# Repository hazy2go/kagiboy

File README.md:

<p align="center">
  <picture>
    <source media="(prefers-color-scheme: dark)" srcset="docs/media/logo-white.png">
    
  </picture>
</p>

<p align="center">
  A hardware wallet that lives in a Game Boy cartridge.<br>
  <a href="https://kagiboy.xyz/demo"><b>Try the live demo</b></a> &nbsp;·&nbsp;
  <a href="https://kagiboy.xyz">Website</a> &nbsp;·&nbsp;
  <a href="https://kagiboy.xyz/about">The story</a> &nbsp;·&nbsp;
  <a href="docs/protocol.md">Protocol</a>
</p>

My dad found my first Game Boy at a flea market. These days the things I care most about are numbers on a phone, and the phone that asks me to approve a transaction is the same phone that tells me what I'm approving. If it lies, I sign the lie.

A Game Boy can't lie to you like that. It has no network, no apps and no operating system. It's a screen and some buttons. So kagiboy puts the keys in a cartridge and uses the Game Boy as the one screen you trust: the cartridge reads every request itself, puts the amount and the full address on that little LCD, and signs only after you hold A. The phone just builds transactions and broadcasts them. It never sees a key.

This repo has all of it: the Game Boy ROM, the cartridge's chip (simulated for now), the phone app, the website, the 3D model and the videos.

> **Status, honestly.** The software is real and runs on testnets today: Solana devnet and five EVM testnets. The ROM runs on a real Game Boy from a flash cart and in your browser. The cartridge itself is in the works; until it ships, its key chip is simulated in the browser. The parts and the plan are in [docs/hardware.md](docs/hardware.md). Please don't put a real recovery phrase anywhere near this.

## Updates

**2026-10-15: the cartridge board.** kagiboy now has its own board, in [`hardware/cart`](hardware/cart/README.md). It's built on our open [WiFi Game Boy Cartridge](https://github.com/hazy2go/wifi-game-boy-cartridge):
- an RP2350B serves the Game Boy's bus;
- an NXP SE050E2 secure element holds the keys and signs;
- a LIS3DH accelerometer adds shake entropy;
- an ESP32-C3 on its own chip does Bluetooth to the phone, so the radio stack never shares a processor with the wallet;
- a power stage that can't pull the Game Boy's 5 V below 4.588 V.

It's placed and routed, and it passes every design check and simulation: ERC/DRC, schematic-to-board parity, I²C and power calculations, the transistor-level power audits, and the cycle-level bus simulation with the real ROM. It isn't ordered yet: one inductor is out of stock at JLC.

**2026-10-15: the cartridge firmware, first part.** [`firmware/rp2350`](firmware/rp2350/README.md), Rust, MIT:
- **The wallet logic,** ported from the browser chip. It's checked against recorded sessions of the browser chip
  and gives identical bytes: every reply, refusal and signature.
- **The firmware that serves the Game Boy bus** with the exact PIO programs the cycle-level simulation validated
  for this board.

**2026-10-15: keys in the secure element.** At setup the firmware imports the two account keys into the NXP SE050
as keys that can only sign, makes the PIN an SE050 object that allows five attempts, and keeps no recovery words. A
key signs only inside a session opened with that PIN. The SE050 driver is our own, MIT. Without a chip, it's tested
against a behavioural SE050 model: every recorded browser session replays through it byte for byte.

**2026-10-15: the Bluetooth link.** The phone app can now talk to a real cartridge: "Use a real cartridge" on the
connect screen (Chrome or Edge, on a computer or Android). Messages go phone → Bluetooth LE → the ESP32-C3, which
passes them over SPI to the RP2350, unchanged. The wallet answers and the reply comes back the same way. The ESP never
sees a key or a PIN. Spec: [docs/phone-link.md](docs/phone-link.md). Every phone call of the recorded sessions goes
through the whole chain in the tests: the web app's bytes, the ESP's C code and the RP2350's Rust code, with damaged
and missed transfers and restarts on both chips. Every reply matches the browser chip's. Not yet run on hardware.

**2026-10-15: the accelerometer.** The LIS3DH is read at 100 Hz into the Game Boy's mailbox, at the same scale the
browser demo gets from the phone's motion sensor, so the ROM's "shake it" step works the same on the real cartridge.
With that, every part of the board has firmware.

**2026-10-16: JLC manufacturability check.** A new gate runs KiCad's DRC at JLCPCB's published 6-layer limits
instead of comparing against the WiFi board. It found three things the WiFi board also has, now fixed:
- a row of ground vias 0.01 mm too close to the top edge;
- ground planes that came within 0.12 mm of the edge;
- the repo URL on the back at 0.8 mm text (JLC's minimum is 1 mm).

The board passes, and the gerbers are regenerated. Every other check, simulation and test was re-run and passes.

**2026-10-16: an independent review against the datasheets.** A fresh reviewer, without our notes or checks,
went through the schematic and board pin by pin against every datasheet. It found problems our checks couldn't
see, and they're fixed:
- the Bluetooth radio's ground was connected but weak (long thin traces, 3 vias in the whole area): it now has a
  ground pour and 77 more vias;
- copper sat under the RP2350's own regulator, which its datasheet forbids on multi-layer boards: cut away, and two
  traces re-routed around it;
- one resistor JLC couldn't supply (swapped for the same value in stock), a missing pull-down on the level shifter,
  and the crystal Raspberry Pi recommends instead of a higher-resistance one;
- the 480 Mb/s USB lines now run side by side on one layer over solid ground.

Everything else it checked came out right. Details in [the logbook](hardware/cart/LOGBOOK.md).

**2026-10-16: the first order is 2 boards.** The parts check now counts stock for 2 assembled boards. Everything
is in stock except the RP2350's regulator inductor (4 left at JLC, we need 7 with spares). We're keeping that exact
part and waiting for a restock.

Next: building the board. It waits for one inductor to come back in stock at JLC. Then firmware on real hardware.

## See it work

<table>
  <tr>
    <td width="62%"></td>
    <td width="38%"></td>
  </tr>
  <tr>
    <td>The phone asks for 0.05 SOL. The Game Boy shows what the chip decoded.</td>
    <td>Hold A for a second. Signed, then confirmed on devnet.</td>
  </tr>
</table>

That transfer is a real devnet transaction: [GeVGY7kn…wEM7BDtK on the Solana explorer](https://explorer.solana.com/tx/GeVGY7kn36SS1aoRXbDQo8WiwukHD4XpPiuzs3X6jpgkfGJWR1dPgesg2B4Dwk2wuS7ngjqYkWEWH11wEM7BDtK?cluster=devnet). Same signature the Game Boy printed.

## Try it

Open **[kagiboy.xyz/demo](https://kagiboy.xyz/demo)**, on a laptop or a phone. It takes about two minutes.

1. Switch on, press Start, pick **New wallet**.
2. Mash buttons, then hold **shake**. Write down the 12 words (they're test words, but play along) and pick a PIN.
3. In the phone app, tap **Pair cartridge**. The same six digits show up on both screens. Press A.
4. Get some devnet SOL with **Get test SOL**, then **Send**. Read what the Game Boy says, hold A.

Keys on a laptop: arrows, `X` = A, `Z` = B, `Enter` = Start, `Shift` = Select. On a phone, tap the console. The bus monitor under the Game Boy shows every message between the console and the chip, with the PIN and the words blanked out.

## How it works

There are three parts, and only the cartridge ever holds a key.

The Game Boy ROM (`rom/`, C with GBDK-2020) is the screen and the buttons. It never touches a key. A Game Boy has exactly one wire to the outside world, the cartridge slot, so that's what we use: the ROM writes a command into a 256-byte mailbox in cartridge memory, and the chip writes its answer back into the same window. Each side owns its own bytes, and the sequence number is written last, so a half-written reply is never read. The commands are in [docs/protocol.md](docs/protocol.md).

The cartridge chip (`web/src/chip/`) holds the keys, counts PIN tries, keeps a network allowlist and its own token list, and decodes and signs. In the demo it's TypeScript running in your browser. On the real cartridge it's an RP2350 with the keys in an NXP SE050 secure element.

The phone app (`web/src/phone/`, `web/src/app/`) talks to the networks: balances, building transactions, broadcasting them. It reaches the chip over Bluetooth on hardware (a function call in the demo) and only ever gets public data back. It's never trusted.

### Signing on Solana

This is the part I care about most. The phone builds a normal `SystemProgram.transfer` and hands over the serialized message bytes, nothing else. The chip copies those bytes, so nothing can change them later, and decodes them itself: the fee payer has to be this cartridge, there has to be exactly one instruction, it has to be a plain transfer from this wallet, and the amount and full address have to fit on the Game Boy screen. If any of that fails, there's no prompt at all. You hold A, the chip signs those exact bytes with ed25519, and the phone broadcasts.

The phone can't fake the result either. It reports a status, but the Game Boy only shows "confirmed" next to the signature the chip itself produced (`setTxStatus` in [chip.ts](web/src/chip/chip.ts)).

### Keys

Every button press and every shake goes to the chip as entropy and gets folded into a SHA-256 pool, which is mixed with the chip's own random generator when the wallet is created. Out come 12 standard BIP-39 words. Solana keys use SLIP-10 ed25519 on Phantom's path (`m/44'/501'/0'/0'`), EVM keys use MetaMask's (`m/44'/60'/0'/0/0`), so the words restore in any normal wallet. The PIN is entered twice and stored salted and hashed. Five wrong tries and the cartridge wipes itself, like a Ledger.

### What it refuses

If the chip can't show something in full, it won't sign it. Those are the chip's real error messages, captured by sending it those requests.

### EVM and swaps

The same 12 words cover Ethereum Sepolia, Base Sepolia, Arbitrum Sepolia, HyperEVM testnet and Robinhood Chain testnet, and LEFT/RIGHT on the Game Boy switches between them. The chip checks the chain id against its allowlist and refuses any fee above 0.01 of the network's coin.

Swaps come from the [SODAX](https://sodax.com) SDK with live quotes. The phone only names tokens by address; symbols, decimals and fees come from the cartridge's own list ([tokens.ts](web/src/chip/tokens.ts)), and the Game Boy shows the least you'll get, after every fee. In the demo, swaps are signed but never sent.

## It runs on a real Game Boy

These are photos of my own DMG running the ROM from an EverDrive. A flash cart has no key chip, so `make demo` builds the prototype with a test chip inside the ROM, generated from the real chip code. It saves the wallet and PIN to the cartridge's battery RAM and plays a little chiptune of mine on the menus. It holds no real keys; it's there so the whole flow can be walked through on a real Game Boy while the cartridge is in the works.

## Build it

The ROM needs [GBDK-2020](https://github.com/gbdk-2020/gbdk-2020). The Makefile looks in `~/gbdk`; override it with `make GBDK=/path/to/gbdk`.

```sh
cd rom
make          # build/wallet.gb, also copied to web/public/wallet.gb
make demo     # build/wallet-demo.gb, the flash-cart prototype build
```

The website and demo are Vite + React + TypeScript.

```sh
cd web
pnpm i
pnpm dev               # then open /demo
pnpm build
pnpm smoke smoke-out   # the real ROM against the chip, headless
```

The smoke test is the thing I trust most in this repo. It boots the real ROM in the emulator and drives it like a person would: setup, reading the Game Boy's QR codes back, signing a SOL transfer and an ETH transfer and checking both signatures, rejecting one, making sure the phone can't put its own words on the screen, signing on HyperEVM, pulling the power mid-request, wiping after five wrong PINs, and restoring a BIP-39 test vector letter by letter. It saves a PNG of every screen and fails loudly.

Everything runs without API keys. The only one is the waitlist on the website, which needs Upstash credentials (`vercel env pull`).

## What's where

| Path | What |
|---|---|
| [`rom/`](rom) | The Game Boy ROM, in C. Setup, entropy, words, PIN, restore with word suggestions, QR codes, hold-to-sign, network switching, pairing. |
| [`web/`](web) | The website and the demo. The chip lives in `src/chip/`, the phone side in `src/phone/` and `src/app/`. |
| [`native/`](native) | A Capacitor shell that packages the demo as an iOS and Android app. No native Bluetooth yet. |
| [`assets/`](assets) | The Blender model and scripts, product renders, the logo and the social card. |
| [`video/`](video) | Both submission videos, built in Remotion, plus the scripts that recorded the demo footage. |
| [`docs/`](docs) | Protocol, hardware, roadmap, four rounds of audits, the pitch material. |
| [`hardware/cart/`](hardware/cart) | The cartridge board (KiCad), its fab files, design checks and power simulations. [`hardware/sim/`](hardware/sim) is the cycle-level bus simulation. |

## Security model, and what isn't solved yet

kagiboy is built to hold up against three things: someone who steals the cartridge, a compromised phone asking for something you didn't mean, and someone listening to the Bluetooth link. What you approve is what the chip decoded and drew on the Game Boy, and only the A button on the Game Boy approves it.

What isn't solved, in the demo:

- The browser demo keeps the recovery phrase in `localStorage`, in plain text. It uses the same derivation paths as Phantom and MetaMask, so a real phrase typed in here maps to your real accounts. Test words only. The ROM says so before a restore.
- A Solana transaction doesn't say which cluster it's for, so the chip can't prove a malicious phone didn't use a mainnet blockhash. EVM is different: there the chip enforces the chain id.
- There's no auto-lock. The chip stays unlocked while it has power.
- Approving signs whatever request is pending. That's safe today because the phone can't replace or cancel a pending request, but it should be bound to a digest of what was shown before any queueing is added.
- On OP-stack chains like Base, the L1 data fee is charged outside gas times max fee, so "MAX" isn't a strict cap there. It's around 2×10⁻¹⁶ ETH on Base Sepolia.
- Balances come from the phone. The chip formats them but can't verify them.
- Swaps get live quotes from SODAX, and the cartridge decodes each one against its own token list and signs it. This build doesn't submit the signed swap to SODAX yet; that's the next step.
- `pnpm audit --prod` reports 8 advisories, all deep inside the `@sodax/sdk` dependency tree. Same-major fixes are pinned; the rest need an SDK update. The SDK only loads on the swap screen.

And in the hardware design:

- Transaction decoding, the fee cap and the PIN session run on the RP2350, not inside the secure element. The SE050 stops keys being extracted, not misuse by compromised firmware. The plan is signed firmware, the Bluetooth stack in TrustZone's non-secure world, and a potted board.
- The SE050 can't derive BIP-32 or SLIP-10 keys, so the seed lives on the MCU during setup. The plan is to derive once, import the keys into the secure element and erase the seed.
- The PIN and the words cross the cartridge bus in plain text, and a modified console could fake button presses. Use your own, unmodified Game Boy.
- The cartridge is in the works and nothing has had an outside security review yet. Nobody should store real money on this until the audited cartridge ships.

The four audit rounds are in [docs/audits](docs/audits). The path to a cartridge you can actually buy is in [docs/ROADMAP.md](docs/ROADMAP.md).

## Thanks, and licenses

kagiboy is [MIT licensed](LICENSE). The `/demo` page bundles the [serverboy](https://gitlab.com/piglet-plays/serverboy.js) emulator (built on Grant Galitz's GameBoy-Online), which is GPL-2.0, so that one bundle is distributed under GPL-2.0. [NOTICE](NOTICE) has the details and the other third-party licenses. The ROM is built with GBDK-2020, the pixel font is Pixel Operator (CC0), and swaps run on SODAX.

Game Boy is a trademark of Nintendo. kagiboy isn't affiliated with Nintendo, and it's a hackathon project for the Colosseum Crypto World's Fair, not a product you can buy yet.

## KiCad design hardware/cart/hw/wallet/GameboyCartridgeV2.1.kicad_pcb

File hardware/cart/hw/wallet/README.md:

# kagiboy wallet cartridge: KiCad project

Status (2026-10-15): 6-layer 0.8 mm, placed, routed and tidied, all checks green. Not ordered yet
(`fab/ORDER.md`). Overview, checks and history: `../README.md` and `../LOGBOOK.md`.

Based on the [WiFi Game Boy Cartridge](https://github.com/hazy2go/wifi-game-boy-cartridge) Rev B board, which
documents where its own design comes from. Hardware licence: CERN Open Hardware Licence v2 Permissive
(`LICENSE-CERN-OHL-P.md`), inherited from that design.

What's here:
- `GameboyCartridgeV2.1.kicad_*`: the schematic (root, `cpu`, `power`, and `radio`, which holds the radio,
  power stage and wallet parts) and the board.
- `radio.kicad_sym`, `radio.pretty`: project symbols and footprints, generated by `tools/gen_radio_symbols.py`,
  `tools/gen_radio_footprints.py`, `tools/gen_wallet_footprints.py`. The added parts' sheet is generated from
  `../docs/design/netlist_radio.json` by `tools/gen_radio_sheet.py`.
- `fab/`: JLC order files.
- `art/`: the back-silkscreen logo source.
- `tools/`: placement, routing, clean-up, audits and fab tools. Each is documented at the top of the file.

Rules for changes:
- Change the design through `../docs/design/netlist_radio.json` and the tools, then run the checks in `../README.md`.
- Log every decision and result in `../LOGBOOK.md`.

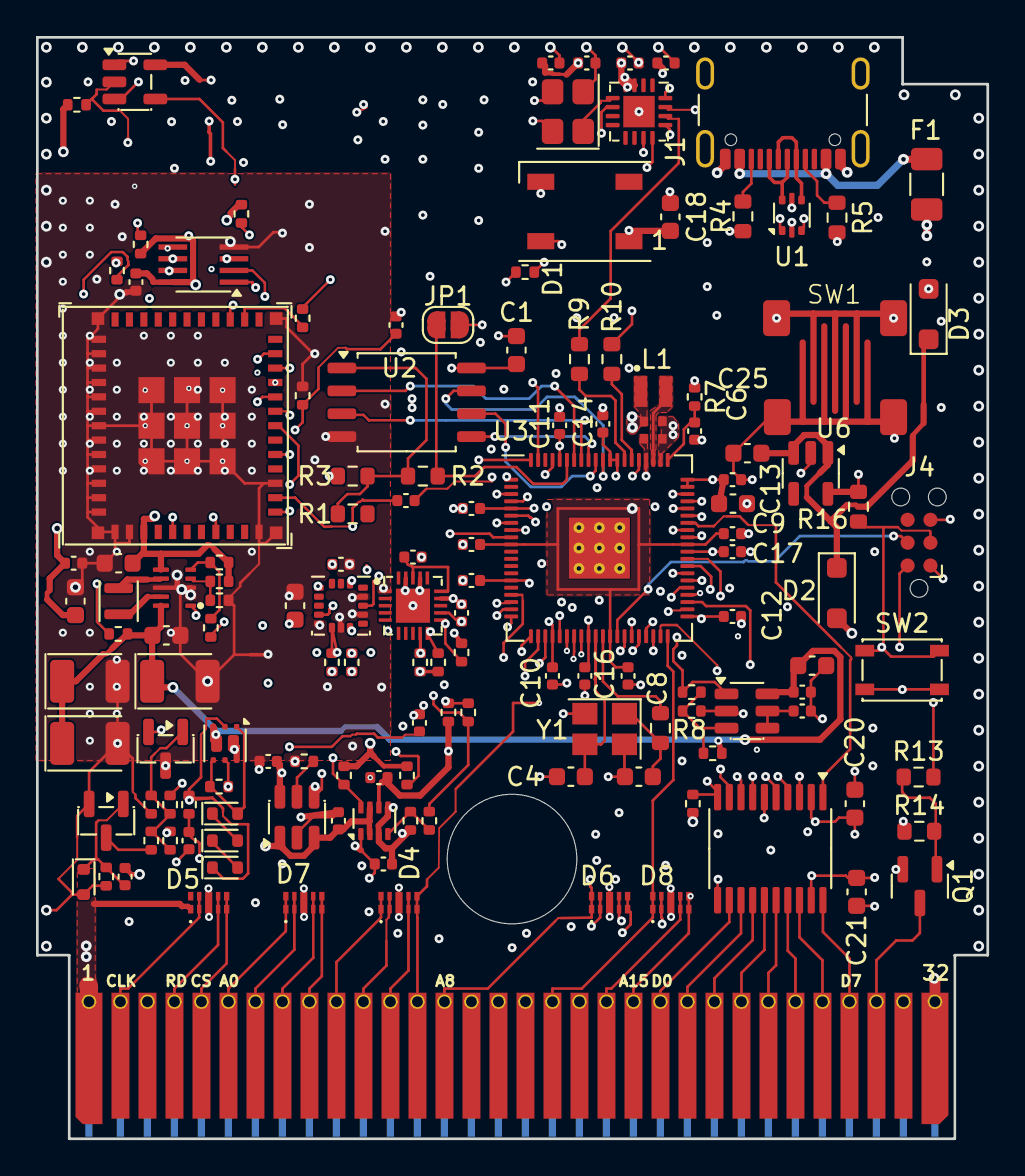
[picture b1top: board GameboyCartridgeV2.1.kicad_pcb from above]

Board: 6 copper layers, 52.8 x 61.2 mm, 140 parts (0 on the bottom side), 124 nets.

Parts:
C1, C18, C20, C21: 100nF; C_0603_1608Metric
C2, C3: 4.7u; C_0402_1005Metric_small_pads
C4, C5: 15pF; C_0603_1608Metric
C6, C8: 4.7u; C_0402_1005Metric
C7, C9, C10, C11, C12, C13, C14, C15, C16, C17, C19: 100n; C_0402_1005Metric
C25, C26: 1uF; C_0603_1608Metric
C101, C102, C103, C104, C118, C119: 1uF 25V X5R; C_0402_1005Metric
C105, C106, C107: 330uF 6.3V 40mOhm T520B337M006ATE040; CP_EIA-3528-21_Kemet-B
C108, C109, C111, C128: 10uF 10V X5R; C_0603_1608Metric
C110: 22uF 6.3V X5R; C_0603_1608Metric
C112, C113, C116, C117, C120, C122, C124, C125, C126, C127: 100nF 16V X7R; C_0402_1005Metric
C114, C115: 2.2nF 50V X7R; C_0402_1005Metric
C121: 10nF 50V X7R; C_0402_1005Metric
C123: 470pF 50V C0G; C_0402_1005Metric
D1: WS2812B; LED_WS2812B_PLCC4_5.0x5.0mm_P3.2mm
D2, D3: D_Schottky; D_SOD-123F
D4, D5, D6, D7, D8: AOZ8809DI-05; TVS_AOZ8809DI-05
D101, D102, D103, D104: 1N4148WT; D_SOD-523
F1: Polyfuse; Fuse_1206_3216Metric
J1: USB_C_Receptacle_USB2.0; USB_C_Receptacle_GCT_USB4105-xx-A_16P_TopMnt_Horizontal
J4: Conn_01x06; Tag-Connect_TC2030-IDC-NL_2x03_P1.27mm_Vertical
J5: CartBus; GameBoy_Cartridge_EdgeConnector
JP1: USB_BOOT_SEL; SolderJumper-2_P1.3mm_Open_RoundedPad1.0x1.5mm
L1: 3.3u; L_pol_2016
L101: 0.47uH 5.5A 26mOhm DFE201612E-R47M; L_Murata_DFE201610P
Q1: CJ2302; SOT-23
Q101: SIA975DJ-T1-GE3; Vishay_PowerPAK_SC70-6L_Dual
Q102: 2N7002; SOT-23
R1, R2: 0R; R_0603_1608Metric
R3, R14, R16: 10k; R_0603_1608Metric
R4, R5: 5k1; R_0603_1608Metric
R7: 33; R_0402_1005Metric
R8, R13: 1k; R_0603_1608Metric
R9, R10: 27R; R_0603_1608Metric
R101: 1.3k 1%; R_0402_1005Metric
R102: 510 1%; R_0402_1005Metric
R103: 180k 1%; R_0402_1005Metric
R104, R115: 100k 1%; R_0402_1005Metric
R108, R111, R112, R113, R114: 10k 1%; R_0402_1005Metric
R109: 511k 1%; R_0402_1005Metric
R110: 91k 1%; R_0402_1005Metric
R116, R118: 680k 1%; R_0402_1005Metric
R117, R119: 200k 1%; R_0402_1005Metric
R120, R121: 22R 1%; R_0402_1005Metric
R122: 33R 1%; R_0402_1005Metric
R123: 1.3M 1%; R_0402_1005Metric
R124: 1.0M 1%; R_0402_1005Metric
R125: 1.2M 1%; R_0402_1005Metric
R126: 27.0k 0.1%; R_0402_1005Metric
R127: 10.0k 0.1%; R_0402_1005Metric
R128, R129: 680 1%; R_0402_1005Metric
R130: 330k 1%; R_0402_1005Metric
R131: 470k 1%; R_0402_1005Metric
R132: 1k 1%; R_0402_1005Metric
R133, R134: 2.2k; R_0402_1005Metric
R135: 100k; R_0402_1005Metric
R136, R137, R138: 4.7k; R_0402_1005Metric
SW1: SW_Push; GameBoy_soft_button
SW2: SW_Push; SW_SPST_PTS810
U1: USBLC6-2P6; SOT-666
U2: W25Q128JVSIQ; SOIC-8_5.23x5.23mm_P1.27mm
U3: RP2350_80QFN; RP2350-QFN-80-1EP_10x10_P0.4mm_EP3.4x3.4mm_ThermalVias
U6: AP2112K-3.3; SOT-23-5
U7: TXB0108PW; TSSOP-20_4.4x6.5mm_P0.65mm
U101: TPS2116DRLR; SOT-583-8
U102: TPS2553DBVR; SOT-23-6
U103: TPS63802DLAR; TI_DLA0010A_VSON-HR-10_2x3mm_P0.5mm
U104: ESP32-C3-MINI-1U-N4; ESP32-C3-MINI-1U
U105: SN74LVC1G125DBVR; SOT-23-5
U106: SN74LVC3G34DCTR; SSOP-8_2.95x2.8mm_P0.65mm
U107: CH334P; QFN-16-1EP_3x3mm_P0.5mm_EP1.75x1.75mm
U108: TLV3012BIDBVR; SOT-23-6
U109: TLV431BIDBZR; SOT-23
U110: SE050E2HQ1/Z01Z3Z; NXP_HX2QFN-20-1EP_3x3mm_P0.4mm_EP1.9x1.9mm
U111: LIS3DHTR; LGA-16_3x3mm_P0.5mm_LayoutBorder3x5y
Y1: 12MHz; Crystal_SMD_TXC_7M-4Pin_3.2x2.5mm
Y101: 12MHz 10pF 10ppm; Crystal_SMD_3225-4Pin_3.2x2.5mm

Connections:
+1V1: C3.1, C7.1, C8.1, C9.1, L1.1, U3.10 (DVDD), U3.32 (DVDD), U3.51 (DVDD), U3.65 (VREG_FB)
+3V3: C1.2, C2.1, C10.1, C11.1, C12.1, C13.1, C14.1, C15.1, C16.1, C17.1, C18.2, C19.1, C20.2, C26.2, C116.1, C118.1, C119.1, C120.1, C125.1, C127.1, C128.1, D1.1 (VDD), J4.1, R3.2, R7.1, R14.1, R16.2, R133.1, R134.1, R136.1, R137.1, U2.8 (VCC), U3.5 (IOVDD), U3.15 (IOVDD), U3.24 (IOVDD), U3.29 (IOVDD), U3.41 (IOVDD), U3.50 (IOVDD), U3.59 (ADC_AVDD), U3.60 (IOVDD), U3.64 (VREG_VIN), U3.68 (USB_OTP_VDD), U3.69 (QSPI_IOVDD), U3.76 (IOVDD), U6.5 (VOUT), U7.2 (VCCA), U105.5, U107.15, U107.16, U110.12, U111.1, U111.8, U111.14
+5V: C25.2, D2.1 (K), D3.1 (K), U6.1 (VIN), U6.3 (EN)
/CPU/FLASH_SS: R1.2, R2.2, R3.1, U2.1 (~CS)
/CPU/VBUS_raw: F1.2, J1.A4 (VBUS), J1.A9 (VBUS), J1.B4 (VBUS), J1.B9 (VBUS)
/CPU/VREG_AVDD: C6.1, R7.2, U3.61 (VREG_AVDD)
/CPU/VREG_LX: L1.2, U3.63 (VREG_LX)
/Radio/+3V3_RF: C110.1, C111.1, C112.1, C117.1, R104.1, R108.1, R109.1, R112.1, R113.1, R114.1, R115.1, U103.6, U104.3, U106.8
/Radio/ADC_VCC: C115.1, R118.2, R119.1, U104.13
/Radio/ADC_VRES: C114.1, R116.2, R117.1, U104.12
/Radio/ESP_CS: U104.16, U106.2
/Radio/ESP_EN: C113.1, R111.2, U104.8
/Radio/ESP_IO2_MISO: R112.2, U104.5, U105.2
/Radio/ESP_IO8: R113.2, U104.22
/Radio/ESP_IO9: R114.2, U104.23
/Radio/ESP_MOSI: U104.21, U106.5
/Radio/ESP_SCK: R122.2, U104.20
/Radio/ESP_SCK_BUF: R122.1, U106.7
/Radio/ESP_USB_DM: R121.2, U104.26
/Radio/ESP_USB_DP: R120.2, U104.27
/Radio/HUB_P2_DM: R121.1, U107.7
/Radio/HUB_P2_DP: R120.1, U107.8
/Radio/HUB_XI: U107.2, Y101.3
/Radio/HUB_XO: U107.1, Y101.1
/Radio/LIM_FAULT_N: R104.2, U102.4, U104.18
/Radio/LIM_ILIM: R103.1, U102.5
/Radio/MUX_PR1: R101.2, R102.1, U101.4
/Radio/PG_REF: C121.1, U108.4, U108.5
/Radio/PG_SENSE: R123.2, R124.1, R125.2, U108.3
/Radio/REG_CCN: C123.2, R130.1
/Radio/REG_CL1: D101.1, D102.2
/Radio/REG_CL2: D102.1, D103.2
/Radio/REG_G: D103.1, Q101.2, Q101.5, R128.2, R129.1
/Radio/REG_K: C123.1, R129.2, U109.2
/Radio/REG_POR_G: C124.2, D104.1, Q102.1, R131.1
/Radio/REG_REF: R126.2, R127.1, R130.2, R132.1, U109.1
/Radio/REG_RSS: Q102.3, R132.2
/Radio/REG_S: D101.2, Q101.1, Q101.4, R128.1
/Radio/RF_EN: R125.1, U103.1, U108.1
/Radio/RF_FB: R109.2, R110.1, U103.4
/Radio/RF_L1: L101.1, U103.9
/Radio/RF_L2: L101.2, U103.7
/Radio/RF_PG: R108.2, R111.1, U103.5
/Radio/SE_VCC: C126.1, U110.15, U110.18
/Radio/USB_PWR_ST: R115.2, U101.8, U104.19
/Radio/VMUX: C103.1, C124.1, R126.1, U101.2, U101.7, U102.1, U102.3
ACC_INT1: U3.9 (GPIO11), U111.11
ACC_SCL: R137.2, U3.7 (GPIO9), U111.4
ACC_SDA: R136.2, U3.6 (GPIO8), U111.6
BUS_RST: R13.2, U3.56 (GPIO45_ADC5)
BUTTON: SW1.1, U3.1 (GPIO4)
DATA_BUS0: U3.45 (GPIO36), U7.9 (A8)
DATA_BUS1: U3.46 (GPIO37), U7.8 (A7)
DATA_BUS2: U3.47 (GPIO38), U7.7 (A6)
DATA_BUS3: U3.48 (GPIO39), U7.6 (A5)
DATA_BUS4: U3.49 (GPIO40_ADC0), U7.5 (A4)
DATA_BUS5: U3.52 (GPIO41_ADC1), U7.4 (A3)
DATA_BUS6: U3.53 (GPIO42_ADC2), U7.3 (A2)
DATA_BUS7: U3.54 (GPIO43_ADC3), U7.1 (A1)
DEBUG_UART_TX: U3.57 (GPIO46_ADC6), U105.1, U106.6
GBBUS_EN: R138.1, U3.55 (GPIO44_ADC4), U7.10 (OE)
GB_A0: D7.1, D7.10, J5.6 (A0), U3.20 (GPIO20)
GB_A1: D7.2, D7.9, J5.7 (A1), U3.21 (GPIO21)
GB_A2: D7.4, D7.7 (NC), J5.8 (A2), U3.22 (GPIO22)
GB_A3: D7.5, D7.6 (NC), J5.9 (A3), U3.23 (GPIO23)
GB_A4: D4.1, D4.10, J5.10 (A4), U3.25 (GPIO24)
GB_A5: D4.2, D4.9, J5.11 (A5), U3.26 (GPIO25)
GB_A6: D4.4, D4.7 (NC), J5.12 (A6), U3.27 (GPIO26)
GB_A7: D4.5, D4.6 (NC), J5.13 (A7), U3.28 (GPIO27)
GB_A8: D6.1, D6.10, J5.14 (A8), U3.36 (GPIO28)
GB_A9: D6.2, D6.9, J5.15 (A9), U3.37 (GPIO29)
GB_A10: D6.4, D6.7 (NC), J5.16 (A10), U3.38 (GPIO30)
GB_A11: D6.5, D6.6 (NC), J5.17 (A11), U3.39 (GPIO31)
GB_A12: D8.1, D8.10, J5.18 (A12), U3.40 (GPIO32)
GB_A13: D8.2, D8.9, J5.19 (A13), U3.42 (GPIO33)
GB_A14: D8.4, D8.7 (NC), J5.20 (A14), U3.43 (GPIO34)
GB_A15: D8.5, D8.6 (NC), J5.21 (A15), U3.44 (GPIO35)
GB_CLK: D5.2, D5.9, J5.2 (CLK~), U3.17 (GPIO17)
GB_CS: D5.5, D5.6 (NC), J5.5 (CS), U3.19 (GPIO19)
GB_D0: J5.22 (D0), U7.12 (B8)
GB_D1: J5.23 (D1), U7.13 (B7)
GB_D2: J5.24 (D2), U7.14 (B6)
GB_D3: J5.25 (D3), U7.15 (B5)
GB_D4: J5.26 (D4), U7.16 (B4)
GB_D5: J5.27 (D5), U7.17 (B3)
GB_D6: J5.28 (D6), U7.18 (B2)
GB_D7: J5.29 (D7), U7.20 (B1)
GB_RD: D5.4, D5.7 (NC), J5.4 (RD), U3.18 (GPIO18)
GB_RST: J5.30 (RST), Q1.3 (D)
GND: C1.1, C2.2, C3.2, C4.1, C5.1, C6.2, C7.2, C8.2, C9.2, C10.2, C11.2, C12.2, C13.2, C14.2, C15.2, C16.2, C17.2, C18.1, C19.2, C20.1, C21.1, C25.1, C26.1, C101.2, C102.2, C103.2, C104.2, C105.2, C106.2, C107.2, C108.2, C109.2, C110.2, C111.2, C112.2, C113.2, C114.2, C115.2, C116.2, C117.2, C118.2, C119.2, C120.2, C121.2, C122.2, C125.2, C126.2, C127.2, C128.2, D1.3 (VSS), D4.3_8, D5.3_8, D6.3_8, D7.3_8, D8.3_8, D104.2, J1.A1 (GND), J1.A12 (GND), J1.B1 (GND), J1.B12 (GND), J1.S1 (SHIELD), J4.5, J5.32 (GND), JP1.2 (B), Q1.2 (S), Q102.2, R4.2, R5.2, R102.2, R103.2, R110.2, R117.2, R119.2, R124.2, R127.2, R131.2, R135.2, R138.2, SW1.2, SW2.2, U1.2 (GND), U2.4 (GND), U3.62 (VREG_PGND), U3.81 (GND), U6.2 (GND), U7.11 (GND), U101.1, U102.2, U103.2, U103.3, U103.8, U104.1, U104.2, U104.11, U104.14, U104.36, U104.37, U104.38, U104.39, U104.40, U104.41, U104.42, U104.43, U104.44, U104.45, U104.46, U104.47, U104.48, U104.49, U104.50, U104.51, U104.52, U104.53, U105.3, U106.4, U107.17, U108.2, U109.3, U110.1, U110.14, U110.17, U110.19, U110.21, U111.5, U111.7, U111.10, U111.12, Y1.2, Y1.4, Y101.2, Y101.4
LED_DIN: D1.4 (DIN), U3.58 (GPIO47_ADC7)
unnamed: C5.2, R8.2, Y1.1
unnamed: J1.A5 (CC1), R5.1
unnamed: J1.B5 (CC2), R4.1
unnamed: Q1.1 (G), R13.1, R14.2
unnamed: R10.1, U3.66 (USB_DM)
unnamed: R9.1, U3.67 (USB_DP)
unnamed: C4.2, U3.30 (XIN), Y1.3
unnamed: R8.1, U3.31 (XOUT)
QSPI_SCLK: U2.6 (CLK), U3.71 (QSPI_SCLK)
QSPI_SD0: U2.5 (DI(IO0)), U3.72 (QSPI_SD0)
QSPI_SD1: U2.2 (DO(IO1)), U3.74 (QSPI_SD1)
QSPI_SD2: U2.3 (IO2), U3.73 (QSPI_SD2)
QSPI_SD3: U2.7 (IO3), U3.70 (QSPI_SD3)
QSPI_SS: JP1.1 (A), R2.1, U3.75 (QSPI_SS)
RST: J4.3, R16.1, SW2.1, U3.35 (RUN)
SE_ENA: R135.1, U3.8 (GPIO10), U110.11
SE_SCL: R134.2, U3.4 (GPIO7), U110.10
SE_SDA: R133.2, U3.3 (GPIO6), U110.9
SPI_CLK: U3.79 (GPIO2), U106.1
SPI_MISO: U3.77 (GPIO0), U105.4
SPI_MOSI: U3.80 (GPIO3), U106.3
SWCLK: J4.4, U3.33 (SWCLK)
SWDIO: J4.2, U3.34 (SWD)
USB_D+: J1.A6 (D+), J1.B6 (D+), U1.6 (I/O1)
USB_D-: J1.A7 (D-), J1.B7 (D-), U1.4 (I/O2)
USB_D_prot+: U1.1 (I/O1), U107.12
USB_D_prot-: U1.3 (I/O2), U107.11
USB_RP_D+: R9.2, U107.10
USB_RP_D-: R10.2, U107.9
VBUS: C101.1, D3.2 (A), F1.1, R101.1, U1.5 (VBUS), U101.3, U101.5
VCC: C21.2, C102.1, D2.2 (A), D5.1, J5.1 (VCC), R118.1, U7.19 (VCCB), U101.6
VLIM: C104.1, Q101.6, U102.6
VRES: C105.1, C106.1, C107.1, C108.1, C109.1, C122.1, Q101.3, R116.1, R123.1, U103.10, U108.6

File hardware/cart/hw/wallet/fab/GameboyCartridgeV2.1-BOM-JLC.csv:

Comment,Designator,Footprint,LCSC Part #
100nF,"C1,C18,C20,C21",C_0603_1608Metric,C14663
4.7u,"C2,C3",C_0402_1005Metric_small_pads,C23733
15pF,"C4,C5",C_0603_1608Metric,C1644
4.7u,"C6,C8",C_0402_1005Metric,C23733
100n,"C7,C9,C10,C11,C12,C13,C14,C15,C16,C17,C19",C_0402_1005Metric,C1525
1uF,"C25,C26",C_0603_1608Metric,C15849
1uF 25V X5R,"C101,C102,C103,C104,C118,C119",C_0402_1005Metric,C52923
330uF 6.3V 40mOhm T520B337M006ATE040,"C105,C106,C107",CP_EIA-3528-21_Kemet-B,C696806
10uF 10V X5R,"C108,C109,C111,C128",C_0603_1608Metric,C19702
22uF 6.3V X5R,C110,C_0603_1608Metric,C59461
100nF 16V X7R,"C112,C113,C116,C117,C120,C122,C124,C125,C126,C127",C_0402_1005Metric,C1525
2.2nF 50V X7R,"C114,C115",C_0402_1005Metric,C84703
10nF 50V X7R,C121,C_0402_1005Metric,C15195
470pF 50V C0G,C123,C_0402_1005Metric,C76971
WS2812B,D1,LED_WS2812B_PLCC4_5.0x5.0mm_P3.2mm,C2761795
D_Schottky,"D2,D3",D_SOD-123F,C669022
1N4148WT,"D101,D102,D103,D104",D_SOD-523,C27748
Polyfuse,F1,Fuse_1206_3216Metric,C2649911
USB_C_Receptacle_USB2.0,J1,USB_C_Receptacle_GCT_USB4105-xx-A_16P_TopMnt_Horizontal,C2927037
3.3u,L1,L_pol_2016,C42411119
0.47uH 5.5A 26mOhm DFE201612E-R47M,L101,L_Murata_DFE201610P,C668312
CJ2302,Q1,SOT-23,C8548
SIA975DJ-T1-GE3,Q101,Vishay_PowerPAK_SC70-6L_Dual,C141597
2N7002,Q102,SOT-23,C8545
0R,R2,R_0603_1608Metric,C21189
10k,"R3,R14,R16",R_0603_1608Metric,C25804
5k1,"R4,R5",R_0603_1608Metric,C23186
33,R7,R_0402_1005Metric,C25105
1k,"R8,R13",R_0603_1608Metric,C21190
27R,"R9,R10",R_0603_1608Metric,C25190
1.3k 1%,R101,R_0402_1005Metric,C25866
510 1%,R102,R_0402_1005Metric,C25123
180k 1%,R103,R_0402_1005Metric,C25760
100k 1%,"R104,R115",R_0402_1005Metric,C25741
10k 1%,"R108,R111,R112,R113,R114",R_0402_1005Metric,C25744
511k 1%,R109,R_0402_1005Metric,C64042
91k 1%,R110,R_0402_1005Metric,C453777
680k 1%,"R116,R118",R_0402_1005Metric,C4131
200k 1%,"R117,R119",R_0402_1005Metric,C25764
22R 1%,"R120,R121",R_0402_1005Metric,C25092
33R 1%,R122,R_0402_1005Metric,C25105
1.3M 1%,R123,R_0402_1005Metric,C423245
1.0M 1%,R124,R_0402_1005Metric,C26083
1.2M 1%,R125,R_0402_1005Metric,C43675
27.0k 0.1%,R126,R_0402_1005Metric,C723421
10.0k 0.1%,R127,R_0402_1005Metric,C190095
680 1%,"R128,R129",R_0402_1005Metric,C137948
330k 1%,R130,R_0402_1005Metric,C25778
470k 1%,R131,R_0402_1005Metric,C25790
1k 1%,R132,R_0402_1005Metric,C11702
2.2k,"R133,R134",R_0402_1005Metric,C25879
100k,R135,R_0402_1005Metric,C25741
4.7k,"R136,R137,R138",R_0402_1005Metric,C25900
USBLC6-2P6,U1,SOT-666,C2827693
W25Q128JVSIQ,U2,SOIC-8_5.23x5.23mm_P1.27mm,C97521
RP2350_80QFN,U3,RP2350-QFN-80-1EP_10x10_P0.4mm_EP3.4x3.4mm_ThermalVias,C42415655
AP2112K-3.3,U6,SOT-23-5,C51118
TXB0108PW,U7,TSSOP-20_4.4x6.5mm_P0.65mm,C53406
TPS2116DRLR,U101,SOT-583-8,C3235557
TPS2553DBVR,U102,SOT-23-6,C55266
TPS63802DLAR,U103,TI_DLA0010A_VSON-HR-10_2x3mm_P0.5mm,C2845237
ESP32-C3-MINI-1U-N4,U104,ESP32-C3-MINI-1U,C2911374
SN74LVC1G125DBVR,U105,SOT-23-5,C23654
SN74LVC3G34DCTR,U106,SSOP-8_2.95x2.8mm_P0.65mm,C139356
CH334P,U107,QFN-16-1EP_3x3mm_P0.5mm_EP1.75x1.75mm,C5373042
TLV3012BIDBVR,U108,SOT-23-6,C20345924
TLV431BIDBZR,U109,SOT-23,C398375
SE050E2HQ1/Z01Z3Z,U110,NXP_HX2QFN-20-1EP_3x3mm_P0.4mm_EP1.9x1.9mm,C5190917
LIS3DHTR,U111,LGA-16_3x3mm_P0.5mm_LayoutBorder3x5y,C15134
12MHz,Y1,Crystal_SMD_TXC_7M-4Pin_3.2x2.5mm,C20625731
12MHz 10pF 10ppm,Y101,Crystal_SMD_3225-4Pin_3.2x2.5mm,C668845

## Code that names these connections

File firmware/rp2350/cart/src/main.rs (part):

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//! The CPU drains the ring into the Game Boy's half of the mailbox and runs the wallet (`kagiboy-core`), whose
//! replies appear in the ROM window at 0x7F00 for the next Game Boy read.
//!
//! Keys and PIN live in the SE050 (I2C1 on GPIO6/7, enable on GPIO10) through `Se050Vault`; the flash record holds
//! no secret. The phone reaches the wallet through the ESP32-C3 (Bluetooth), which offers its messages on SPI0
//! (GPIO0 MISO, GPIO2 SCK, GPIO3 MOSI, CS GPIO46): `link::LinkMaster` polls it every millisecond and
//! `phone::PhoneServer` answers (docs/phone-link.md). The LIS3DH (I2C0 on GPIO8/9) is read at 100 Hz into the
//! mailbox's ACCEL_X / ACCEL_Y, which the ROM turns into shake entropy.
#![no_std]
#![no_main]
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    // Hold the Game Boy in reset until the bus is served; the boot ROM reads the cartridge header immediately.
    let mut gb_reset = Output::new(p.PIN_45, Level::High);
    let _bus_enable = Output::new(p.PIN_44, Level::High); // TXB0108 OE
    let esp_cs = Output::new(p.PIN_46, Level::High); // ESP32-C3 chip select idles high (no pull-up on the board)

    let image = unsafe { &mut *addr_of_mut!(IMAGE.0) };
    image.fill(0xff);
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    info!("bus served from SRAM at {:x}, write ring at {:x}", image_base, ring_base);

    // SE050: enable, let it boot, then the vault opens T=1 and selects the applet on first use
    let se_ena = Output::new(p.PIN_10, Level::High);
    Timer::after_millis(10).await;
    let mut i2c_cfg = i2c::Config::default();
    i2c_cfg.frequency = 1_000_000; // Fm+; the board's 2.2k pull-ups (R133/R134) are sized for it
    i2c_cfg.sda_pullup = false;
    i2c_cfg.scl_pullup = false;
    let se_bus = SeBus { i2c: I2c::new_blocking(p.I2C1, p.PIN_7, p.PIN_6, i2c_cfg), _ena: se_ena };
    let mut chip = Chip::with_vault(FlashStore { flash: Flash::new_blocking(p.FLASH) }, Se050Vault::new(se_bus));
    let mut hw = Hw { trng: Trng::new(p.TRNG, Irqs, trng::Config::default()), epoch_at_boot_ms: 0 };
    let mut mailbox = Mailbox::default();
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}

/// /RD as the `jmp pin` of state machine `sm`. embassy-rp 0.10 can't set it here: its config field is private and
/// it would write the absolute GPIO number, while the hardware counts from GPIOBASE (16), so 18 would mean GPIO34.
fn set_jmp_pin(sm: usize) {
    pac::PIO0.sm(sm).execctrl().modify(|w| w.set_jmp_pin(PIO_PIN_RD));
}
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
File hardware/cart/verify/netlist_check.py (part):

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  MULTI_DRIVER     two different parts with output/power_out pins on one net
  REF_DUP          duplicated reference, or a reference that clashes with a Croco reference
  BOM              missing/invalid LCSC number or footprint; footprint not found in KiCad libs
  STRAP            ESP32-C3 strapping pin GPIO2/GPIO8/GPIO9 without a defined boot level
                   (required: GPIO2=1, GPIO8=1, GPIO9=1 -> SPI boot, ESP32-C3-MINI-1 DS Table 4-3)
  CROCO_EDIT       a croco_edits entry that does not match the Croco netlist

Usage:
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
KNOWN_SOURCES = {'GND', 'VCC', 'VBUS', '+3V3'}      # supplied by Croco / the cartridge slot / USB
DRIVER_TYPES = {'output', 'power_out'}
STRAPS = {'IO2': '1', 'IO8': '1', 'IO9': '1'}       # ESP32-C3 SPI boot (Table 4-3), GPIO8=1 for download
ESP_SYMBOL = 'radio:ESP32-C3-MINI-1U'

# ------------------------------------------------------------------ s-expressions / KiCad libs
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        part(d, 'C117')['pins']['1'] = 'SELFTEST_UNPOWERED'

    def m_two_drivers(d):
        part(d, 'U108')['pins']['1'] = 'VMUX'

    def m_dup_ref(d):
        part(d, 'R102')['ref'] = 'R101'
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
    def m_strap_missing(d):
        d['parts'].remove(part(d, 'R112'))
        part(d, 'U104')['pins']['5'] = 'ESP_IO2_MISO'

    def m_power_nc(d):
        part(d, 'U107')['pins']['15'] = 'NC'
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             ('single-pin net', m_single_net, 'SINGLE_NET'), ('unpowered rail', m_no_source, 'NO_SOURCE'),
             ('comparator output onto VMUX', m_two_drivers, 'MULTI_DRIVER'), ('duplicate ref', m_dup_ref, 'REF_DUP'),
             ('Croco ref clash', m_croco_ref, 'REF_DUP'), ('missing LCSC', m_no_lcsc, 'BOM'),
             ('missing footprint', m_bad_fp, 'BOM'), ('GPIO9 strapped low', m_strap_low, 'STRAP'),
             ('GPIO2 pull-up removed', m_strap_missing, 'STRAP'), ('hub V5 NC', m_power_nc, 'POWER_NC'),
             ('unknown symbol', m_bad_symbol, 'SYMBOL'), ('bad Croco edit', m_bad_edit, 'CROCO_EDIT')]
    ok = True
    for label, fn, want in cases:
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
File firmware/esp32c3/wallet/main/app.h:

/* kagiboy radio: the ESP32-C3 passes phone messages between Bluetooth LE and the RP2350 (docs/phone-link.md).
 * Pin map: hardware/cart/docs/design/DESIGN_CALCS.md (U104 table). */
#pragma once

#include <stdbool.h>
#include <stddef.h>
#include <stdint.h>

#include "freertos/FreeRTOS.h"
#include "freertos/semphr.h"
#include "power_mgr.h"
#include "wallet_link.h"

/* U104 pins */
#define PIN_ESP_CS 10    /* FSPICS0, from RP2350 GPIO46 through U106 */
#define PIN_ESP_SCK 6    /* FSPICLK */
#define PIN_ESP_MOSI 7   /* FSPID */
#define PIN_ESP_MISO 2   /* FSPIQ -> U105 (driven only while CS is low) */
#define PIN_USB_PWR_ST 5 /* TPS2116 ST: high = running from USB (VIN1) */
#define PIN_LIM_FAULT 4  /* TPS2553 /FAULT: low = limiter saturated (telemetry) */
/* ADC1_CH0 = IO0 = ADC_VRES, ADC1_CH1 = IO1 = ADC_VCC; dividers 680k / 200k */
#define ADC_DIV_K (200.0f / (680.0f + 200.0f))

/* ---------------------------------------------------------------- link.c */
extern wl_slave_t kgb_link; /* the shipped SPI-slave half, guarded by kgb_link_mtx */
extern SemaphoreHandle_t kgb_link_mtx;
void link_task(void *arg);
void link_pause(bool pause); /* PARK: free the SPI slave so the chip can light-sleep */

/* ---------------------------------------------------------------- ble.c */
void ble_init(void);
void ble_allow(bool on);                         /* advertise / accept a phone only while the power allows */
void ble_send_reply(const uint8_t *msg, size_t len); /* a reply from the RP2350: notify the phone */

/* ---------------------------------------------------------------- power.c */
extern pm_t kgb_pm;
void power_init(void);
void power_task(void *arg);
